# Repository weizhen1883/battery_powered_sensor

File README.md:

# Battery Powered Sensor
This project designed a battery powered IMU sensor. This sensor require to use a IMU, LSM6DSMTR, made by ST. This sensor require to be powered by battery and have a pushbutton to turn on and off.

## Table of Contents
1. [Hardware](hardware/README.md)
2. [Firmware](firmware/README.md)
3. [Parts Specifications](#parts-specifications)
4. [Operational Specifications](#operational-specifications)

## Parts Specifications
1. MCU
 - Chip Number: nRF52832
 - Module Number: PTR5618
2. Button
 - Single pole, momentary, normally open type
3. IMU
 - Part Number: [LSM6DSMTR](https://www.st.com/content/ccc/resource/technical/document/datasheet/76/27/cf/88/c5/03/42/6b/DM00218116.pdf/files/DM00218116.pdf/jcr:content/translations/en.DM00218116.pdf)
4. Battery:
 - Part number: [LP501218JH](https://www.jauch.com/downloadfile/5bf52a0e7827c7c5e9e1dbf47ce24c136/60mah_-_lp501218jh_1s1p_2_wire_50mm.pdf)

## Operational Specifications
1. Firmware requirements
 - Configure all that is required to communicate via SPI with the IMU
 - Configure the IMU
 - Sample the IMU at 833 hz, the sampled data can be discarded in this example.
 - ** NOTE: Keep the firmware simple, this is an example project and will not need to be maintained in the future.
2. IMU Configuration
 - SPI communication mode
 - Both accelerometer and gyro data should be sampled
 - Accelerometer range should be set to +-16g
 - Gyro range should be set to +-2000 dps
 - All other settings/features can be disabled or configured as desired/needed.
3. Button Operation
 - From the ‘OFF’ state: Press the button once to switch the device to the ‘ON’ state. The duration of the press is not important or specified.
 - From the ‘ON’ state: Press and hold the button for >500ms to switch the device to the ‘OFF’ state.
4. Power consumption
 - In the ‘OFF’ state, the device should not significantly drain the battery in 1 year. Design should minimize the power off current consumption.
 - In the ‘ON’ state, power consumption is not limited.

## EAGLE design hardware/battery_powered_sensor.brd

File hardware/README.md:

# Battery Powered Sensor Hardware

## Table of Contents
1. [Requirements](#requirements)
2. [Usage](#usage)
3. [Releases](#releases)
4. [Versions](#versions)
5. [Licenses](#licenses)

## Requirements
1. [eagle_pcb_library](https://github.com/weizhen1883/eaglePCBLibrary.git)

## Usage
#### generate PCB files
1. open the battery_powered_sensor.brd file
2. click "CMA Processor"
3. load the CAM.cam file, and click "process job"
4. the PCB files are generated in "outputs" folder

## Releases
#### Release-1
- Version 1.0.0

## Versions
#### Version 1.0.0
- circuits to support nRF52832 module
- boost converter to support 3.3V
- single pushbutton for on/off and normal control
- circuits for IMU, LSM6DSM, in mode1 and using SPI

## Licenses

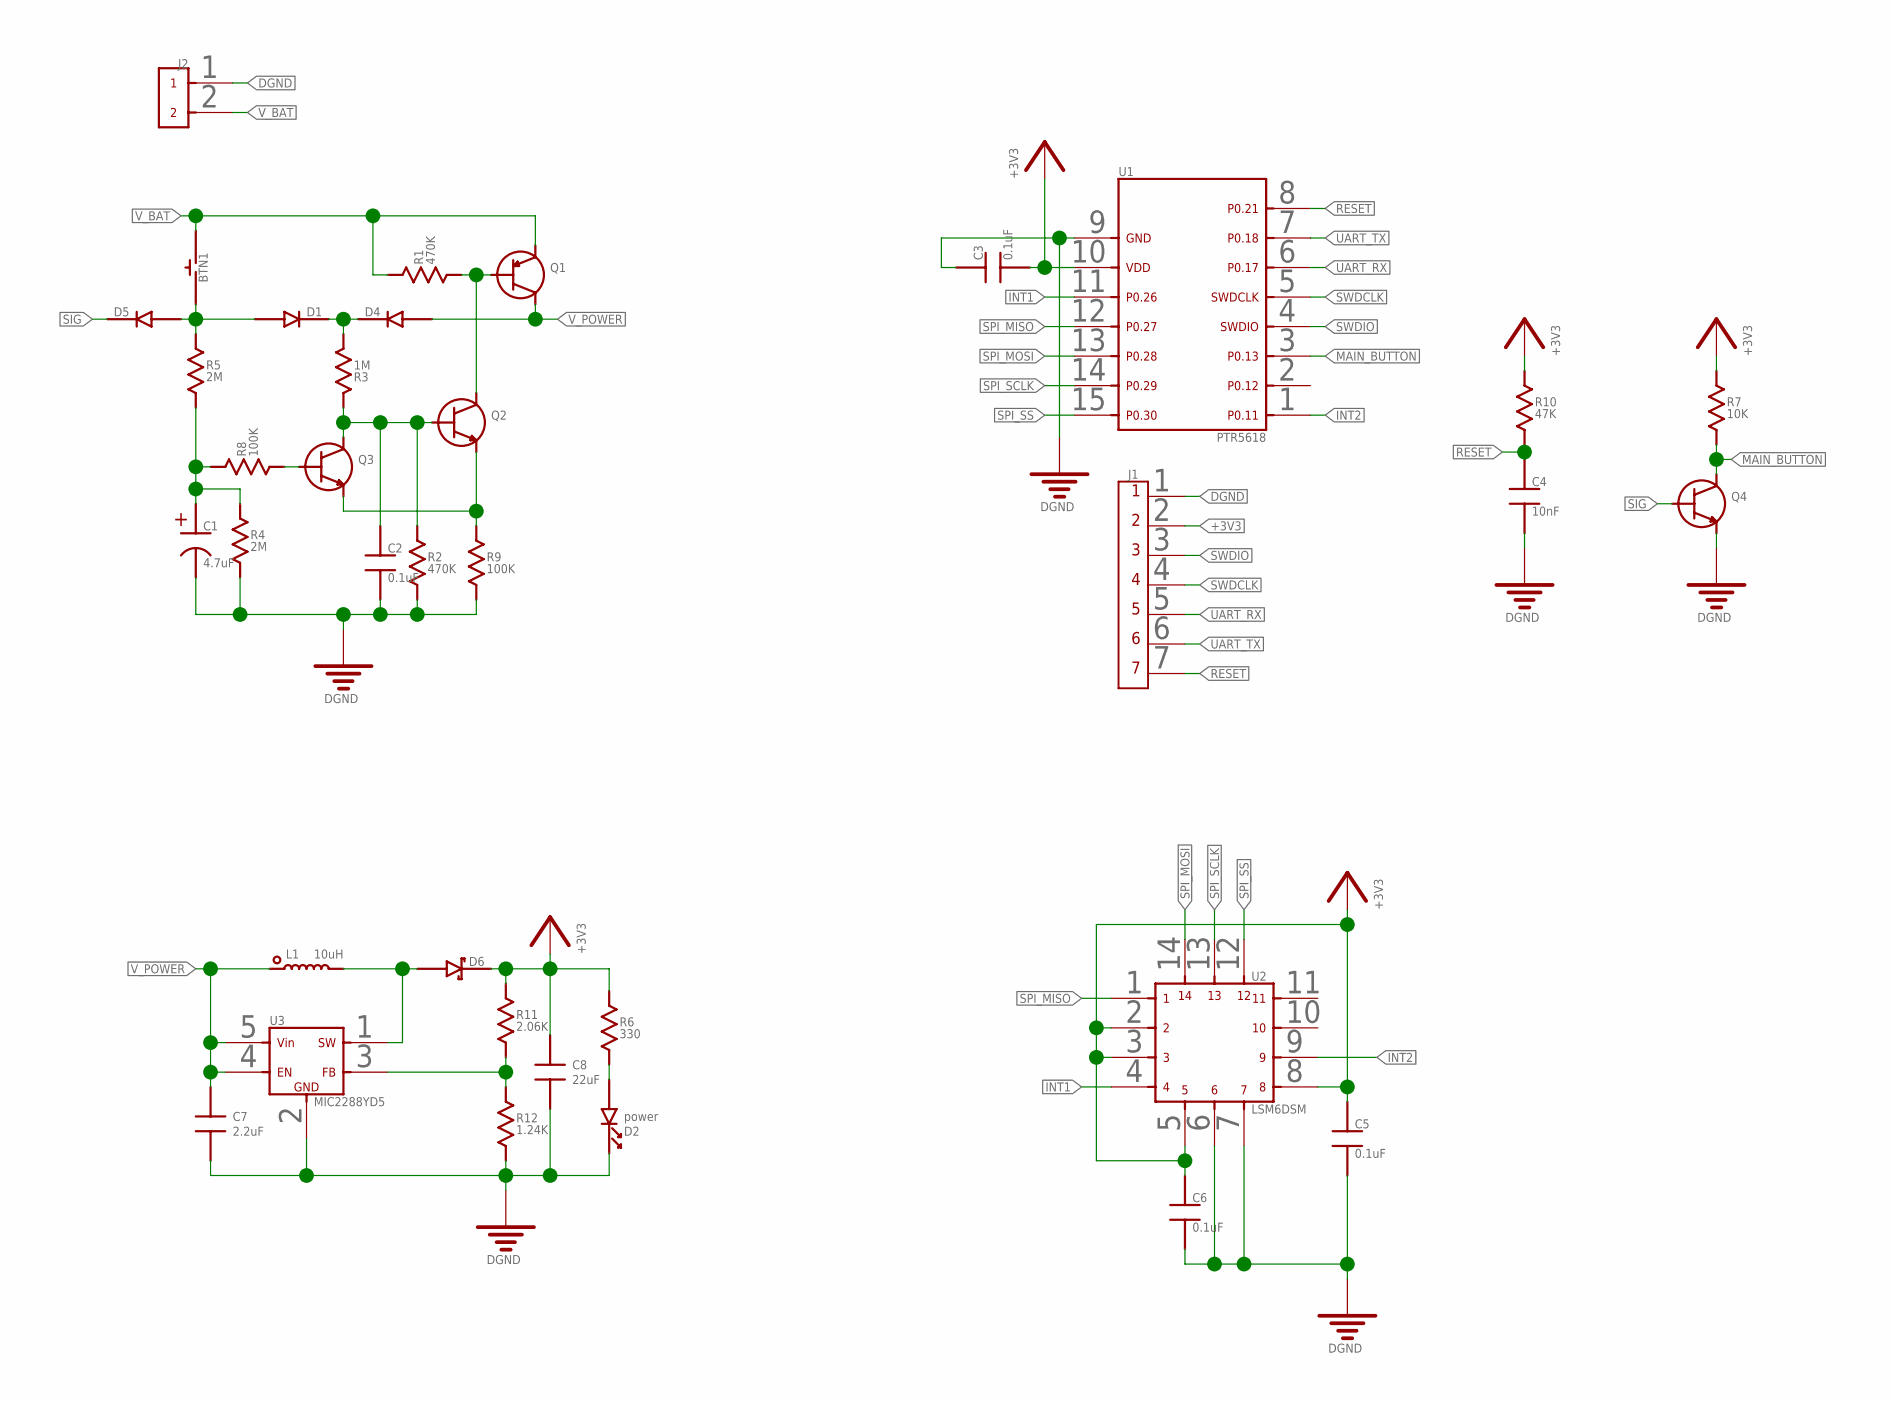
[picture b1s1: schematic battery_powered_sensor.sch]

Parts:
BTN1: BTN_NORMAL_OFF_6_3.5_SMD; BTN_6_3.5_SMD
C1: 4.7uF; CAP_530_530
C2, C3, C5, C6: 0.1uF; 0805
C4: 10nF; 0805
C7: 2.2uF; 0805
C8: 22uF; 0805
D1, D4, D5: DIODE0805; 0805DIODE
D2: power; 0805DIODE
D6: SCHOTTKY_DIODE_0805; 0805DIODE
J1: 7PIN_HEADER_PITCH2.54MM_TH
J2: 2PIN_HEADER_PITCH2.54MM_TH
L1: 10uH; 1008
Q1: MMBT4403; SOT_23_3
Q2, Q3, Q4: BC846; SOT_23_3
R1, R2: 470K; 0805
R3: 1M; 0805
R4, R5: 2M; 0805
R6: 330; 0805
R7: 10K; 0805
R8, R9: 100K; 0805
R10: 47K; 0805
R11: 2.06K; 0805
R12: 1.24K; 0805
U1: PTR5618
U2: LSM6DSM; LGA-14L
U3: MIC2288YD5; SOT-23-5

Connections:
+3V3: C3.2, C5.1, C6.1, C8.1, D6.1, J1.2, R6.1, R7.1, R10.1, R11.1, U1.10, U2.2, U2.3, U2.5, U2.8
DGND: C1.2, C2.2, C3.1, C4.2, C5.2, C6.2, C7.2, C8.2, D2.1 (K), J1.1, J2.1, Q4.3 (E), R2.2, R4.2, R9.2, R12.2, U1.9, U2.6, U2.7, U3.2 (GND)
INT1: U1.11, U2.4
INT2: U1.1, U2.9
MAIN_BUTTON: Q4.2 (C), R7.2, U1.3
unnamed: D1.1, D4.1, R3.2
unnamed: Q1.1 (B), Q2.2 (C), R1.2
unnamed: Q2.3 (E), Q3.3 (E), R9.1
unnamed: C2.1, Q2.1 (B), Q3.2 (C), R2.1, R3.1
unnamed: D2.2 (A), R6.2
unnamed: C1.1, R4.1, R5.2, R8.1
unnamed: Q3.1 (B), R8.2
unnamed: BTN1.1, D1.2, D5.2, R5.1
unnamed: R11.2, R12.1, U3.3 (FB)
unnamed: D6.2, L1.2, U3.1 (SW)
RESET: C4.1, J1.7, R10.2, U1.8
SIG: D5.1, Q4.1 (B)
SPI_MISO: U1.12, U2.1
SPI_MOSI: U1.13, U2.14
SPI_SCLK: U1.14, U2.13
SPI_SS: U1.15, U2.12
SWDCLK: J1.4, U1.5
SWDIO: J1.3, U1.4
UART_RX: J1.5, U1.6
UART_TX: J1.6, U1.7
V_BAT: BTN1.2, J2.2, Q1.3 (E), R1.1
V_POWER: C7.1, D4.2, L1.1, Q1.2 (C), U3.4 (EN), U3.5 (VIN)

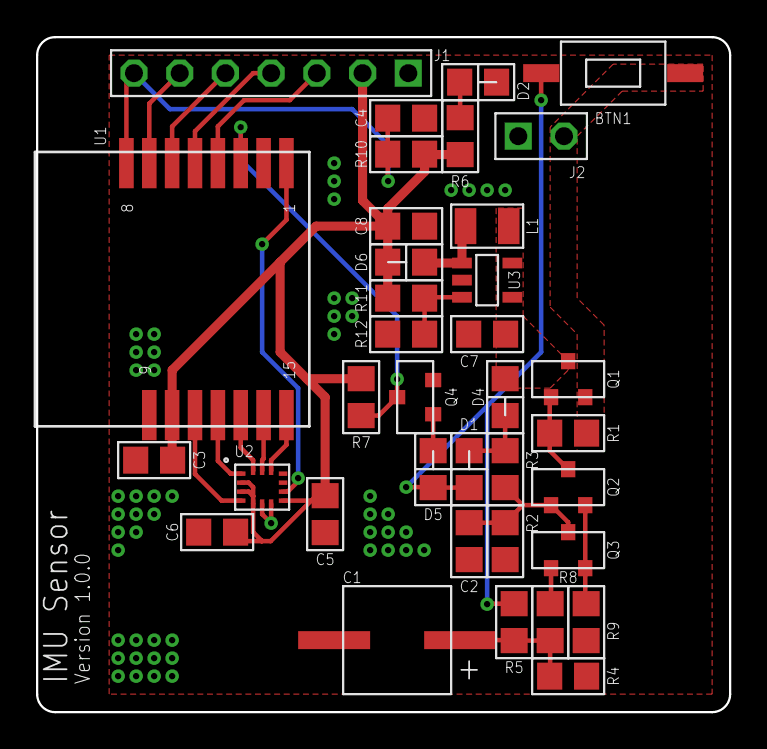
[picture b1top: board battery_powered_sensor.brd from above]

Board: 2 copper layers, 38.5 x 37.5 mm, 36 parts (0 on the bottom side), 27 nets.

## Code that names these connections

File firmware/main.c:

#include <string.h>
#include "nrf.h"
#include "nrf_timer.h"
#include "nrf_gpio.h"
#include "nrf_delay.h"
#include "nrf_log.h"
#include "nrf_log_ctrl.h"
#include "nrf_log_default_backends.h"
#include "nrf_drv_spi.h"
#include "app_util_platform.h"
#include "app_error.h"

#define PIN_SPI_SS          30
#define PIN_SPI_MISO        27
#define PIN_SPI_MOSI        28
#define PIN_SPI_SCK         29

#define LSM6DSM_WRITE_MASK          0x7F
#define LSM6DSM_READ_MASK           0x80

/* ----- LSM6DSM Register Addresses ---- */
#define LSM6DSM_REG_CTRL1_XL    0x10
#define LSM6DSM_REG_CTRL2_G     0x11
#define LSM6DSM_REG_CTRL3_C     0x12
#define LSM6DSM_REG_CTRL4_C     0x13
#define LSM6DSM_REG_CTRL5_C     0x14
#define LSM6DSM_REG_CTRL6_C     0x15
#define LSM6DSM_REG_CTRL7_G     0x16
#define LSM6DSM_REG_CTRL8_XL    0x17
#define LSM6DSM_REG_CTRL9_XL    0x18
#define LSM6DSM_REG_CTRL10_C    0x19

#define LSM6DSM_REG_OUT_TEMP_L  0x20
#define LSM6DSM_REG_OUT_TEMP_H  0x21
#define LSM6DSM_REG_OUTX_L_G    0x22
#define LSM6DSM_REG_OUTX_H_G    0x23
#define LSM6DSM_REG_OUTY_L_G    0x24
#define LSM6DSM_REG_OUTY_H_G    0x25
#define LSM6DSM_REG_OUTZ_L_G    0x26
#define LSM6DSM_REG_OUTZ_H_G    0x27
#define LSM6DSM_REG_OUTX_L_XL   0x28
#define LSM6DSM_REG_OUTX_H_XL   0x29
#define LSM6DSM_REG_OUTY_L_XL   0x2A
#define LSM6DSM_REG_OUTY_H_XL   0x2B
#define LSM6DSM_REG_OUTZ_L_XL   0x2C
#define LSM6DSM_REG_OUTZ_H_XL   0x2D

#define MAX_BUF_LEN     10

#define SPI_INSTANCE  0 /**< SPI instance index. */
static const nrf_drv_spi_t spi = NRF_DRV_SPI_INSTANCE(SPI_INSTANCE);  /**< SPI instance. */
static volatile bool sample_timeout = false;  /**< Flags when sampling timer timeout*/

typedef struct
{
    uint16_t x;
    uint16_t y;
    uint16_t z;
} sensor_data_t;

uint8_t LSM6DSM_write (uint8_t addr, uint8_t * data, uint8_t len)
{
    uint8_t err_code = 0;
    uint8_t tx_buf[MAX_BUF_LEN];
    uint8_t rx_buf[MAX_BUF_LEN];
    memset(tx_buf, 0, MAX_BUF_LEN);
    memset(rx_buf, 0, MAX_BUF_LEN);

    if (MAX_BUF_LEN - 1 < len)
    {
        err_code = 1;
    }
    else
    {
        tx_buf[0] = addr & LSM6DSM_WRITE_MASK;
        memcpy(&tx_buf[1], data, len);

        APP_ERROR_CHECK(nrf_drv_spi_transfer(&spi, tx_buf, len, rx_buf, 0));
    }

    return err_code;
}

uint8_t LSM6DSM_read (uint8_t addr, uint8_t * data, uint8_t len)
{
    uint8_t err_code = 0;
    uint8_t tx_buf[MAX_BUF_LEN];
    uint8_t rx_buf[MAX_BUF_LEN];
    memset(tx_buf, 0, MAX_BUF_LEN);
    memset(rx_buf, 0, MAX_BUF_LEN);

    if (MAX_BUF_LEN - 1 < len)
    {
        err_code = 1;
    }
    else
    {
        tx_buf[0] = addr | LSM6DSM_READ_MASK;

        APP_ERROR_CHECK(nrf_drv_spi_transfer(&spi, tx_buf, 1, rx_buf, len));
    }

    return err_code;
}

void LSM6DSM_settings (void)
{
    // set accelerometer output data rate to 833Hz
    // set accelerometer range to +-16g
    uint8_t accelerometer_settings = 0b01110100; // 0111 for 833hz, 01 for +-16g,
    LSM6DSM_write(LSM6DSM_REG_CTRL1_XL, &accelerometer_settings, 1);

    // set gyroscope output data rate to  833Hz
    // set gyroscope range to +-2000dps
    uint8_t gyroscope_settings = 0b01111100; // 0111 for 833hz, 11 for 2000dps
    LSM6DSM_write(LSM6DSM_REG_CTRL2_G, &gyroscope_settings, 1);

    // disable i2c
    uint8_t control_settings_4 = 0b00000100;
    LSM6DSM_write(LSM6DSM_REG_CTRL4_C, &control_settings_4, 1);
}

uint16_t LSM6DSM_get_output (uint8_t addr)
{
    uint8_t data_buf[2] = { 0x00, 0x00 };
    uint16_t data = 0x0000;
    LSM6DSM_read(addr, &data_buf[0], 2);
    data |= data_buf[1];
    data = (data << 8) | data_buf[0];
    return data;
}

sensor_data_t LSM6DSM_get_gyroscope_output (void)
{
    sensor_data_t data;
    data.x = LSM6DSM_get_output(LSM6DSM_REG_OUTX_L_G);
    data.y = LSM6DSM_get_output(LSM6DSM_REG_OUTY_L_G);
    data.z = LSM6DSM_get_output(LSM6DSM_REG_OUTZ_L_G);
    return data;
}

sensor_data_t LSM6DSM_get_accelerometer_output (void)
{
    sensor_data_t data;
    data.x = LSM6DSM_get_output(LSM6DSM_REG_OUTX_L_XL);
    data.y = LSM6DSM_get_output(LSM6DSM_REG_OUTY_L_XL);
    data.z = LSM6DSM_get_output(LSM6DSM_REG_OUTZ_L_XL);
    return data;
}

void log_info_sensor_data (sensor_data_t data)
{
    uint8_t buf[6] = {
        (data.x >> 8) & 0x00FF, data.x & 0x00FF,
        (data.y >> 8) & 0x00FF, data.y & 0x00FF,
        (data.z >> 8) & 0x00FF, data.z & 0x00FF,
    };
    NRF_LOG_HEXDUMP_INFO(buf, 6);
}

void TIMER2_IRQHandler(void) {
    if ( (NRF_TIMER2->INTENSET & NRF_TIMER_INT_COMPARE0_MASK)
         && (NRF_TIMER2->EVENTS_COMPARE[0] != 0)
       ) {
        NRF_TIMER2->EVENTS_COMPARE[0] = 0;
        NRF_TIMER2->TASKS_CLEAR = 1; /* clear counter */

        sample_timeout = true;
    }
}

int main(void)
{
    sensor_data_t gyroscope_output = { .x = 0, .y = 0, .z = 0 };
    sensor_data_t accelerometer_output = { .x = 0, .y = 0, .z = 0 };

    APP_ERROR_CHECK(NRF_LOG_INIT(NULL));
    NRF_LOG_DEFAULT_BACKENDS_INIT();

    // enable spi
    nrf_drv_spi_config_t spi_config = NRF_DRV_SPI_DEFAULT_CONFIG;
    spi_config.ss_pin   = PIN_SPI_SS;
    spi_config.miso_pin = PIN_SPI_MISO;
    spi_config.mosi_pin = PIN_SPI_MOSI;
    spi_config.sck_pin  = PIN_SPI_SCK;
    APP_ERROR_CHECK(nrf_drv_spi_init(&spi, &spi_config, NULL, NULL));

    // configure sampling timer
    NRF_TIMER2->MODE = NRF_TIMER_MODE_TIMER;
    NRF_TIMER2->TASKS_CLEAR = 1;
    NRF_TIMER2->PRESCALER = 4; /* div by 2^x； = 1 MHz */
    NRF_TIMER2->BITMODE = NRF_TIMER_BIT_WIDTH_16;
    NRF_TIMER2->CC[0] = 833; /* 833 Hz */
    NRF_TIMER2->INTENSET = NRF_TIMER_INT_COMPARE0_MASK;
    NVIC_SetPriority(TIMER2_IRQn, 3);
    NVIC_EnableIRQ(TIMER2_IRQn);

    // set LSM6DSM
    LSM6DSM_settings();

    // enable sampling timer
    sample_timeout = false;
    NRF_TIMER2->TASKS_CLEAR = 1;
	NRF_TIMER2->TASKS_START = 1;

    NRF_LOG_INFO("LSM6DSM sensor started.");

    while (1)
    {
        if (sample_timeout)
        {
            gyroscope_output = LSM6DSM_get_gyroscope_output();
            accelerometer_output = LSM6DSM_get_accelerometer_output();

            NRF_LOG_INFO("Gyroscope: ");
            log_info_sensor_data(gyroscope_output);

            NRF_LOG_INFO("Accelerometer: ");
            log_info_sensor_data(accelerometer_output);

            sample_timeout = false;
        }

        NRF_LOG_FLUSH();
    }
}

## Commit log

2021-11-25 init project
2021-11-30 Hardware version 1.0.0
2021-11-30 add submodule nrf5_sdk into project
2021-11-30 Firmware Version 1.0.0
2021-11-30 Release-1
